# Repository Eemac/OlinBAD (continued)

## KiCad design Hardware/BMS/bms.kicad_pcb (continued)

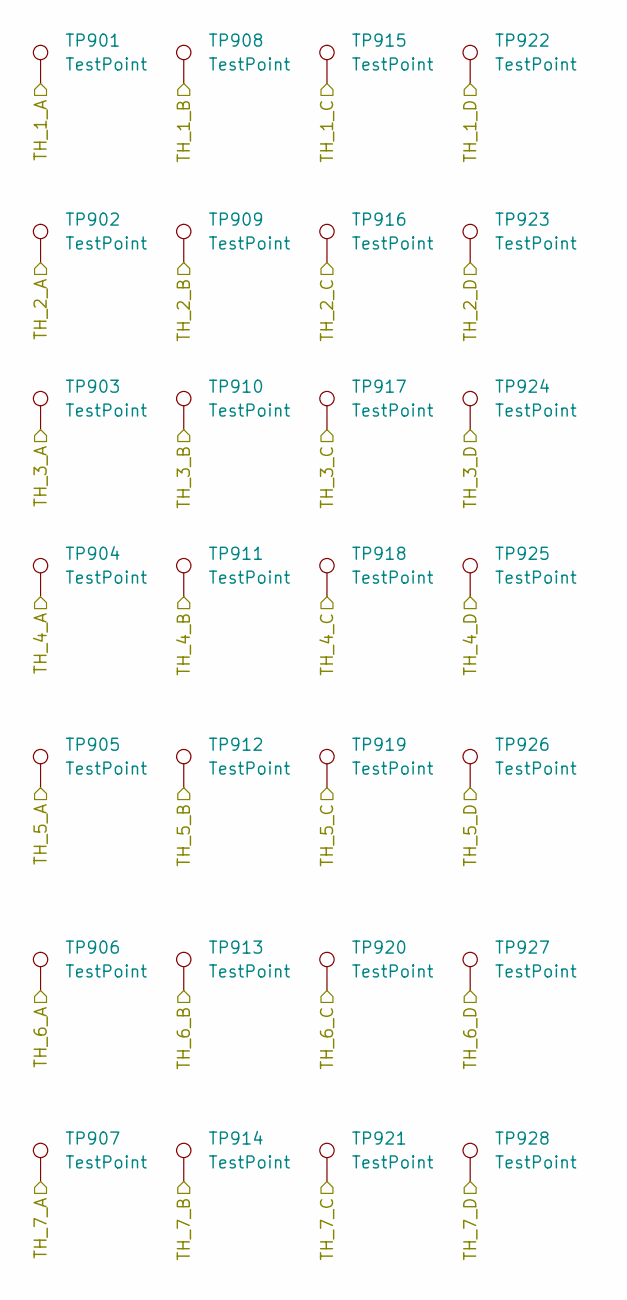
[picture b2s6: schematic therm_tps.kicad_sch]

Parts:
TP901, TP902, TP903, TP904, TP905, TP906, TP907, TP908, TP909, TP910, TP911, TP912, TP913, TP914, TP915, TP916, TP917, TP918, TP919, TP920, TP921, TP922, TP923, TP924, TP925, TP926, TP927, TP928: TestPoint; TestPoint_Pad_1.0x1.0mm

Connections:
/Thermistors/TH_1_A: TP901.1; also elsewhere on the board
/Thermistors/TH_1_B: TP908.1; also elsewhere on the board
/Thermistors/TH_1_C: TP915.1; also elsewhere on the board
/Thermistors/TH_1_D: TP922.1; also elsewhere on the board
/Thermistors/TH_2_A: TP902.1; also elsewhere on the board
/Thermistors/TH_2_B: TP909.1; also elsewhere on the board
/Thermistors/TH_2_C: TP916.1; also elsewhere on the board
/Thermistors/TH_2_D: TP923.1; also elsewhere on the board
/Thermistors/TH_3_A: TP917.1; also elsewhere on the board
/Thermistors/TH_3_B: TP924.1; also elsewhere on the board
/Thermistors/TH_3_C: TP903.1; also elsewhere on the board
/Thermistors/TH_3_D: TP910.1; also elsewhere on the board
/Thermistors/TH_4_A: TP904.1; also elsewhere on the board
/Thermistors/TH_4_B: TP911.1; also elsewhere on the board
/Thermistors/TH_4_C: TP918.1; also elsewhere on the board
/Thermistors/TH_4_D: TP925.1; also elsewhere on the board
/Thermistors/TH_5_A: TP905.1; also elsewhere on the board
/Thermistors/TH_5_B: TP912.1; also elsewhere on the board
/Thermistors/TH_5_C: TP919.1; also elsewhere on the board
/Thermistors/TH_5_D: TP926.1; also elsewhere on the board
/Thermistors/TH_6_A: TP906.1; also elsewhere on the board
/Thermistors/TH_6_B: TP913.1; also elsewhere on the board
/Thermistors/TH_6_C: TP920.1; also elsewhere on the board
/Thermistors/TH_6_D: TP927.1; also elsewhere on the board
/Thermistors/TH_7_A: TP907.1; also elsewhere on the board
/Thermistors/TH_7_B: TP914.1; also elsewhere on the board
/Thermistors/TH_7_C: TP921.1; also elsewhere on the board
/Thermistors/TH_7_D: TP928.1; also elsewhere on the board

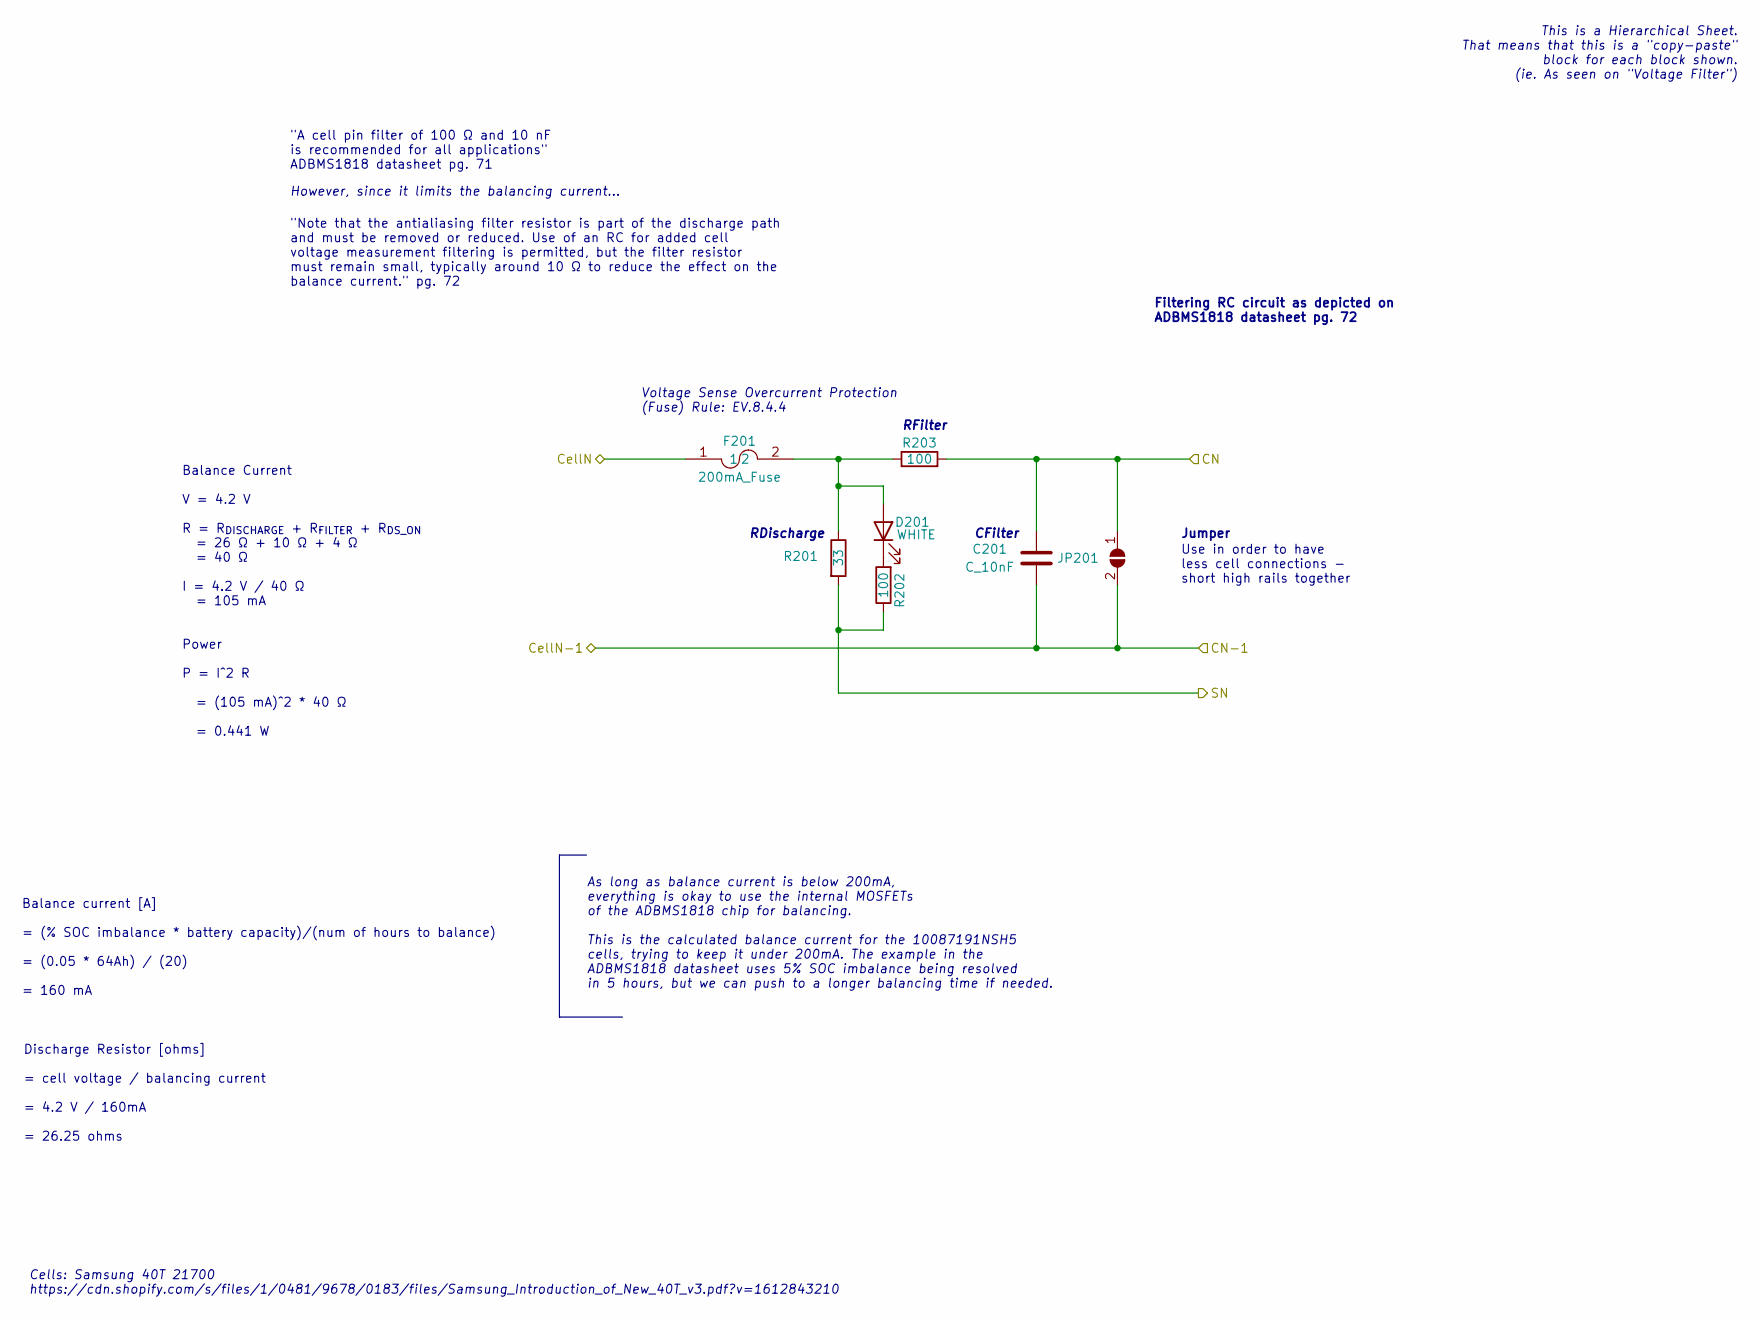
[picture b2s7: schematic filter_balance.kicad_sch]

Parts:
C201: C_10nF; C_0603_1608Metric; MPN CL10B103KB8NNNC
D201: WHITE; LED_0805_2012Metric
F201: 200mA_Fuse; Fuse_1206_3216Metric; MPN 0466.200NRHF
JP201: SolderJumper_2_Open; SolderJumper-2_P1.3mm_Open_TrianglePad1.0x1.5mm
R201: 33; R_2512_6332Metric; MPN 352022RJT
R202: 100; R_0603_1608Metric
R203: 100; R_0603_1608Metric; MPN SG73P1JTTD100J

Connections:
/ADBMS1818/C1: C201.1, F201.1, JP201.1 (A), R203.2; also elsewhere on the board
/ADBMS1818/S1: R201.2, R202.1; also elsewhere on the board
GND: C201.2, JP201.2 (B); also elsewhere on the board
unnamed: D201.2 (A), F201.2, R201.1, R203.1
unnamed: D201.1 (K), R202.2

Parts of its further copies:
C701, C1001, C1201, C1301, C1401, C1501, C1601, C1701, C1801, C1901, C2001, C2101, C2201: C_10nF; C_0603_1608Metric; MPN CL10B103KB8NNNC
D701, D1001, D1201, D1301, D1401, D1501, D1601, D1701, D1801, D1901, D2001, D2101, D2201: WHITE; LED_0805_2012Metric
F701, F1001, F1201, F1301, F1401, F1501, F1601, F1701, F1801, F1901, F2001, F2101, F2201: 200mA_Fuse; Fuse_1206_3216Metric; MPN 0466.200NRHF
JP701, JP1001, JP1201, JP1301, JP1401, JP1501, JP1601, JP1701, JP1801, JP1901, JP2001, JP2101, JP2201: SolderJumper_2_Open; SolderJumper-2_P1.3mm_Open_TrianglePad1.0x1.5mm
R701, R1001, R1201, R1301, R1401, R1501, R1601, R1701, R1801, R1901, R2001, R2101, R2201: 33; R_2512_6332Metric; MPN 352022RJT
R702, R1002, R1202, R1302, R1402, R1502, R1602, R1702, R1802, R1902, R2002, R2102, R2202: 100; R_0603_1608Metric
R703, R1003, R1203, R1303, R1403, R1503, R1603, R1703, R1803, R1903, R2003, R2103, R2203: 100; R_0603_1608Metric; MPN SG73P1JTTD100J

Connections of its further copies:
/ADBMS1818/C1: C701.2, JP701.2 (B); also elsewhere on the board
/ADBMS1818/C2: C701.1, C1001.2, F701.1, JP701.1 (A), JP1001.2 (B), R703.2; also elsewhere on the board
/ADBMS1818/C3: C1001.1, C1201.2, F1001.1, JP1001.1 (A), JP1201.2 (B), R1003.2; also elsewhere on the board
/ADBMS1818/C4: C1201.1, C1301.2, F1201.1, JP1201.1 (A), JP1301.2 (B), R1203.2; also elsewhere on the board
/ADBMS1818/C5: C1301.1, C1401.2, F1301.1, JP1301.1 (A), JP1401.2 (B), R1303.2; also elsewhere on the board
/ADBMS1818/C6: C1401.1, C1501.2, F1401.1, JP1401.1 (A), JP1501.2 (B), R1403.2; also elsewhere on the board
/ADBMS1818/C7: C1501.1, C1601.2, F1501.1, JP1501.1 (A), JP1601.2 (B), R1503.2; also elsewhere on the board
/ADBMS1818/C8: C1601.1, C1701.2, F1601.1, JP1601.1 (A), JP1701.2 (B), R1603.2; also elsewhere on the board
/ADBMS1818/C9: C1701.1, C1801.2, F1701.1, JP1701.1 (A), JP1801.2 (B), R1703.2; also elsewhere on the board
/ADBMS1818/C10: C1801.1, C1901.2, F1801.1, JP1801.1 (A), JP1901.2 (B), R1803.2; also elsewhere on the board
/ADBMS1818/C11: C1901.1, C2001.2, F1901.1, JP1901.1 (A), JP2001.2 (B), R1903.2; also elsewhere on the board
/ADBMS1818/C12: C2001.1, C2101.2, F2001.1, JP2001.1 (A), JP2101.2 (B), R2003.2; also elsewhere on the board
/ADBMS1818/C13: C2101.1, C2201.2, F2101.1, JP2101.1 (A), JP2201.2 (B), R2103.2; also elsewhere on the board
/ADBMS1818/C14: C2201.1, JP2201.1 (A), R2203.2; also elsewhere on the board
/ADBMS1818/CELL14: F2201.1; also elsewhere on the board
/ADBMS1818/S2: R701.2, R702.1; also elsewhere on the board
/ADBMS1818/S3: R1001.2, R1002.1; also elsewhere on the board
/ADBMS1818/S4: R1201.2, R1202.1; also elsewhere on the board
/ADBMS1818/S5: R1301.2, R1302.1; also elsewhere on the board
/ADBMS1818/S6: R1401.2, R1402.1; also elsewhere on the board
/ADBMS1818/S7: R1501.2, R1502.1; also elsewhere on the board
/ADBMS1818/S8: R1601.2, R1602.1; also elsewhere on the board
/ADBMS1818/S9: R1701.2, R1702.1; also elsewhere on the board
/ADBMS1818/S10: R1801.2, R1802.1; also elsewhere on the board
/ADBMS1818/S11: R1901.2, R1902.1; also elsewhere on the board
/ADBMS1818/S12: R2001.2, R2002.1; also elsewhere on the board
/ADBMS1818/S13: R2101.2, R2102.1; also elsewhere on the board
/ADBMS1818/S14: R2201.2, R2202.1; also elsewhere on the board
unnamed: D701.2 (A), F701.2, R701.1, R703.1
unnamed: D701.1 (K), R702.2
unnamed: D1001.2 (A), F1001.2, R1001.1, R1003.1
unnamed: D1001.1 (K), R1002.2
unnamed: D1201.2 (A), F1201.2, R1201.1, R1203.1
unnamed: D1201.1 (K), R1202.2
unnamed: D1301.2 (A), F1301.2, R1301.1, R1303.1
unnamed: D1301.1 (K), R1302.2
unnamed: D1401.2 (A), F1401.2, R1401.1, R1403.1
unnamed: D1401.1 (K), R1402.2
unnamed: D1501.2 (A), F1501.2, R1501.1, R1503.1
unnamed: D1501.1 (K), R1502.2
unnamed: D1601.2 (A), F1601.2, R1601.1, R1603.1
unnamed: D1601.1 (K), R1602.2
unnamed: D1701.2 (A), F1701.2, R1701.1, R1703.1
unnamed: D1701.1 (K), R1702.2
unnamed: D1801.2 (A), F1801.2, R1801.1, R1803.1
unnamed: D1801.1 (K), R1802.2
unnamed: D1901.2 (A), F1901.2, R1901.1, R1903.1
unnamed: D1901.1 (K), R1902.2
unnamed: D2001.2 (A), F2001.2, R2001.1, R2003.1
unnamed: D2001.1 (K), R2002.2
unnamed: D2101.2 (A), F2101.2, R2101.1, R2103.1
unnamed: D2101.1 (K), R2102.2
unnamed: D2201.2 (A), F2201.2, R2201.1, R2203.1
unnamed: D2201.1 (K), R2202.2

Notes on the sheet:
Filtering RC circuit as depicted on ADBMS1818 datasheet pg. 72
"A cell pin filter of 100 Ω and 10 nF is recommended for all applications" ADBMS1818 datasheet pg. 71
Cells: Samsung 40T 21700 https://cdn.shopify.com/s/files/1/0481/9678/0183/files/Samsung_Introduction_of_New_40T_v3.pdf?v=1612843210
Balance current [A] = (% SOC imbalance * battery capacity)/(num of hours to balance) = (0.05 * 64Ah) / (20) = 160 mA
RFilter
Discharge Resistor [ohms] = cell voltage / balancing current = 4.2 V / 160mA = 26.25 ohms
Use in order to have less cell connections - short high rails together
"Note that the antialiasing filter resistor is part of the discharge path and must be removed or reduced. Use of an RC for added cell voltage measurement filtering is permitted, but the filter resistor must remain small, typically around 10 Ω to reduce the effect on the balance current." pg. 72
However, since it limits the balancing current...
RDischarge
Balance Current V = 4.2 V R = R_{DISCHARGE} + R_{FILTER} + R_{DS_ON} = 26 Ω + 10 Ω + 4 Ω = 40 Ω I = 4.2 V / 40 Ω = 105 mA Power P = I^2 R = (105 mA)^2 * 40 Ω = 0.441 W
As long as balance current is below 200mA, everything is okay to use the internal MOSFETs of the ADBMS1818 chip for balancing. This is the calculated balance current for the 10087191NSH5 cells, trying to keep it under 200mA. The example in the ADBMS1818 datasheet uses 5% SOC imbalance being resolve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
This is a Hierarchical Sheet. That means that this is a "copy-paste" block for each block shown. (ie. As seen on "Voltage Filter")
CFilter
Voltage Sense Overcurrent Protection (Fuse) Rule: EV.8.4.4
Jumper

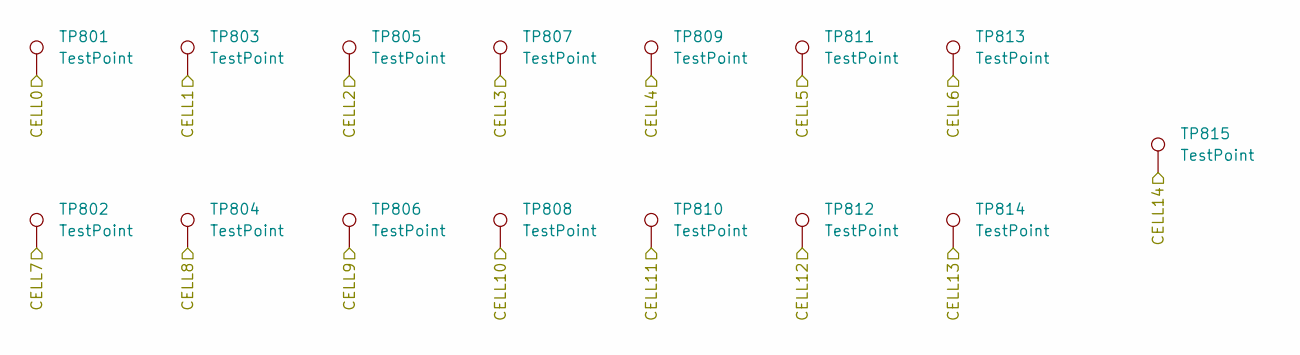
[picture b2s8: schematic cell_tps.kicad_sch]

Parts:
TP801, TP802, TP803, TP804, TP805, TP806, TP807, TP808, TP809, TP810, TP811, TP812, TP813, TP814, TP815: TestPoint; TestPoint_Pad_1.0x1.0mm

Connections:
/ADBMS1818/C1: TP803.1; also elsewhere on the board
/ADBMS1818/C2: TP805.1; also elsewhere on the board
/ADBMS1818/C3: TP807.1; also elsewhere on the board
/ADBMS1818/C4: TP809.1; also elsewhere on the board
/ADBMS1818/C5: TP811.1; also elsewhere on the board
/ADBMS1818/C6: TP813.1; also elsewhere on the board
/ADBMS1818/C7: TP802.1; also elsewhere on the board
/ADBMS1818/C8: TP804.1; also elsewhere on the board
/ADBMS1818/C9: TP806.1; also elsewhere on the board
/ADBMS1818/C10: TP808.1; also elsewhere on the board
/ADBMS1818/C11: TP810.1; also elsewhere on the board
/ADBMS1818/C12: TP812.1; also elsewhere on the board
/ADBMS1818/C13: TP814.1; also elsewhere on the board
/ADBMS1818/CELL14: TP815.1; also elsewhere on the board
GND: TP801.1; also elsewhere on the board

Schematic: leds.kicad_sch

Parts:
D1101, D1104, D1106, D1109, D1111: LED_0805_Red; LED_0805_OEM; MPN 475-1415-1-ND
D1102, D1105, D1108, D1110, D1112: LED_0805; LED_0805_OEM; MPN 475-1410-1-ND
D1103, D1107: LED_0805_Amber; LED_0805_OEM; MPN L71517CT-ND
R1101, R1104, R1106, R1109, R1111: 300; R_0603_1608Metric; MPN 667-ERJ-6ENF1200V
R1102, R1105, R1108, R1110, R1112: 120; R_0603_1608Metric; MPN 667-ERJ-6ENF1200V
R1103, R1107: 220; R_0603_1608Metric; MPN 667-ERJ-6ENF1200V

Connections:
/STM32/ADBMS_COMS: D1110.2 (A); also elsewhere on the board
/STM32/BMS_HEARTBEAT: D1107.2 (A); also elsewhere on the board
/STM32/CAN_COMS: D1102.2 (A); also elsewhere on the board
/STM32/DEBUG1: D1103.2 (A); also elsewhere on the board
/STM32/ERROR: D1111.2 (A); also elsewhere on the board
/STM32/MUX1_COMS: D1105.2 (A); also elsewhere on the board
/STM32/MUX2_COMS: D1108.2 (A); also elsewhere on the board
/STM32/OT: D1106.2 (A); also elsewhere on the board
/STM32/OV: D1101.2 (A); also elsewhere on the board
/STM32/USB_C_COMS: D1112.2 (A); also elsewhere on the board
/STM32/UT: D1109.2 (A); also elsewhere on the board
/STM32/UV: D1104.2 (A); also elsewhere on the board
GND: R1101.2, R1102.2, R1103.2, R1104.2, R1105.2, R1106.2, R1107.2, R1108.2, R1109.2, R1110.2, R1111.2, R1112.2; also elsewhere on the board
unnamed: D1101.1 (K), R1101.1
unnamed: D1102.1 (K), R1102.1
unnamed: D1103.1 (K), R1103.1
unnamed: D1104.1 (K), R1104.1
unnamed: D1105.1 (K), R1105.1
unnamed: D1106.1 (K), R1106.1
unnamed: D1107.1 (K), R1107.1
unnamed: D1108.1 (K), R1108.1
unnamed: D1109.1 (K), R1109.1
unnamed: D1110.1 (K), R1110.1
unnamed: D1111.1 (K), R1111.1
unnamed: D1112.1 (K), R1112.1

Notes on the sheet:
Heartbeat in code

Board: 4 copper layers, 316 parts (0 on the bottom side), 181 nets, no tracks yet.

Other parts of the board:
kibuzzard-68FE96E6: G***; kibuzzard-68FE96E6
kibuzzard-68FE9694: G***; kibuzzard-68FE9694
kibuzzard-68FE9708: G***; kibuzzard-68FE9708

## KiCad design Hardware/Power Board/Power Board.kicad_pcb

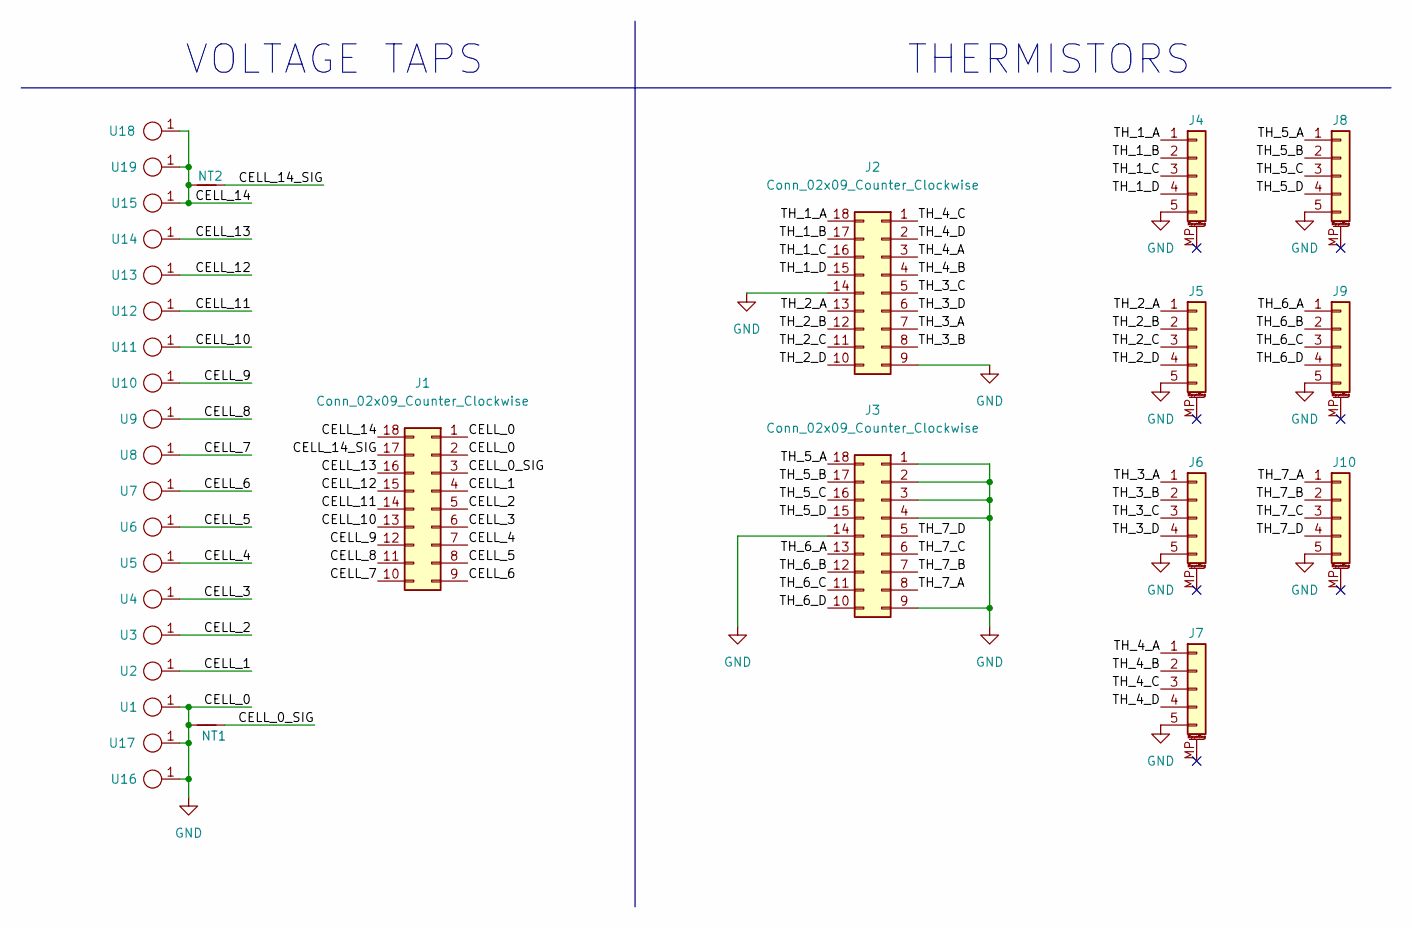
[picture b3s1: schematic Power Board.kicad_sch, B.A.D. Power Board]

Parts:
J1, J2, J3: Conn_02x09_Counter_Clockwise; PinSocket_2x09_P2.54mm_Vertical
J4, J5, J6, J7, J8, J9, J10: Conn_01x05_MountingPin; TE_0-1734839-5_1x05-1MP_P0.5mm_Horizontal
NT1, NT2: NetTie_2; NetTie-2_SMD_Pad0.5mm
U1, U2, U3, U4, U5, U6, U7, U8, U9, U10, U11, U12, U13, U14, U15: BatteryTab
U16, U17, U18, U19: 7461098

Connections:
/CELL_0_SIG: J1.3, NT1.2
/CELL_1: J1.4, U2.1
/CELL_2: J1.5, U3.1
/CELL_3: J1.6, U4.1
/CELL_4: J1.7, U5.1
/CELL_5: J1.8, U6.1
/CELL_6: J1.9, U7.1
/CELL_7: J1.10, U8.1
/CELL_8: J1.11, U9.1
/CELL_9: J1.12, U10.1
/CELL_10: J1.13, U11.1
/CELL_11: J1.14, U12.1
/CELL_12: J1.15, U13.1
/CELL_13: J1.16, U14.1
/CELL_14: J1.18, NT2.2, U15.1, U18.1, U19.1
/CELL_14_SIG: J1.17, NT2.1
/TH_1_A: J2.18, J4.1
/TH_1_B: J2.17, J4.2
/TH_1_C: J2.16, J4.3
/TH_1_D: J2.15, J4.4
/TH_2_A: J2.13, J5.1
/TH_2_B: J2.12, J5.2
/TH_2_C: J2.11, J5.3
/TH_2_D: J2.10, J5.4
/TH_3_A: J2.7, J6.1
/TH_3_B: J2.8, J6.2
/TH_3_C: J2.5, J6.3
/TH_3_D: J2.6, J6.4
/TH_4_A: J2.3, J7.1
/TH_4_B: J2.4, J7.2
/TH_4_C: J2.1, J7.3
/TH_4_D: J2.2, J7.4
/TH_5_A: J3.18, J8.1
/TH_5_B: J3.17, J8.2
/TH_5_C: J3.16, J8.3
/TH_5_D: J3.15, J8.4
/TH_6_A: J3.13, J9.1
/TH_6_B: J3.12, J9.2
/TH_6_C: J3.11, J9.3
/TH_6_D: J3.10, J9.4
/TH_7_A: J3.8, J10.1
/TH_7_B: J3.7, J10.2
/TH_7_C: J3.6, J10.3
/TH_7_D: J3.5, J10.4
GND: J1.1, J1.2, J2.9, J2.14, J3.1, J3.2, J3.3, J3.4, J3.9, J3.14, J4.5, J5.5, J6.5, J7.5, J8.5, J9.5, J10.5, NT1.1, U1.1, U16.1, U17.1

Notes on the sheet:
THERMISTORS
VOLTAGE TAPS

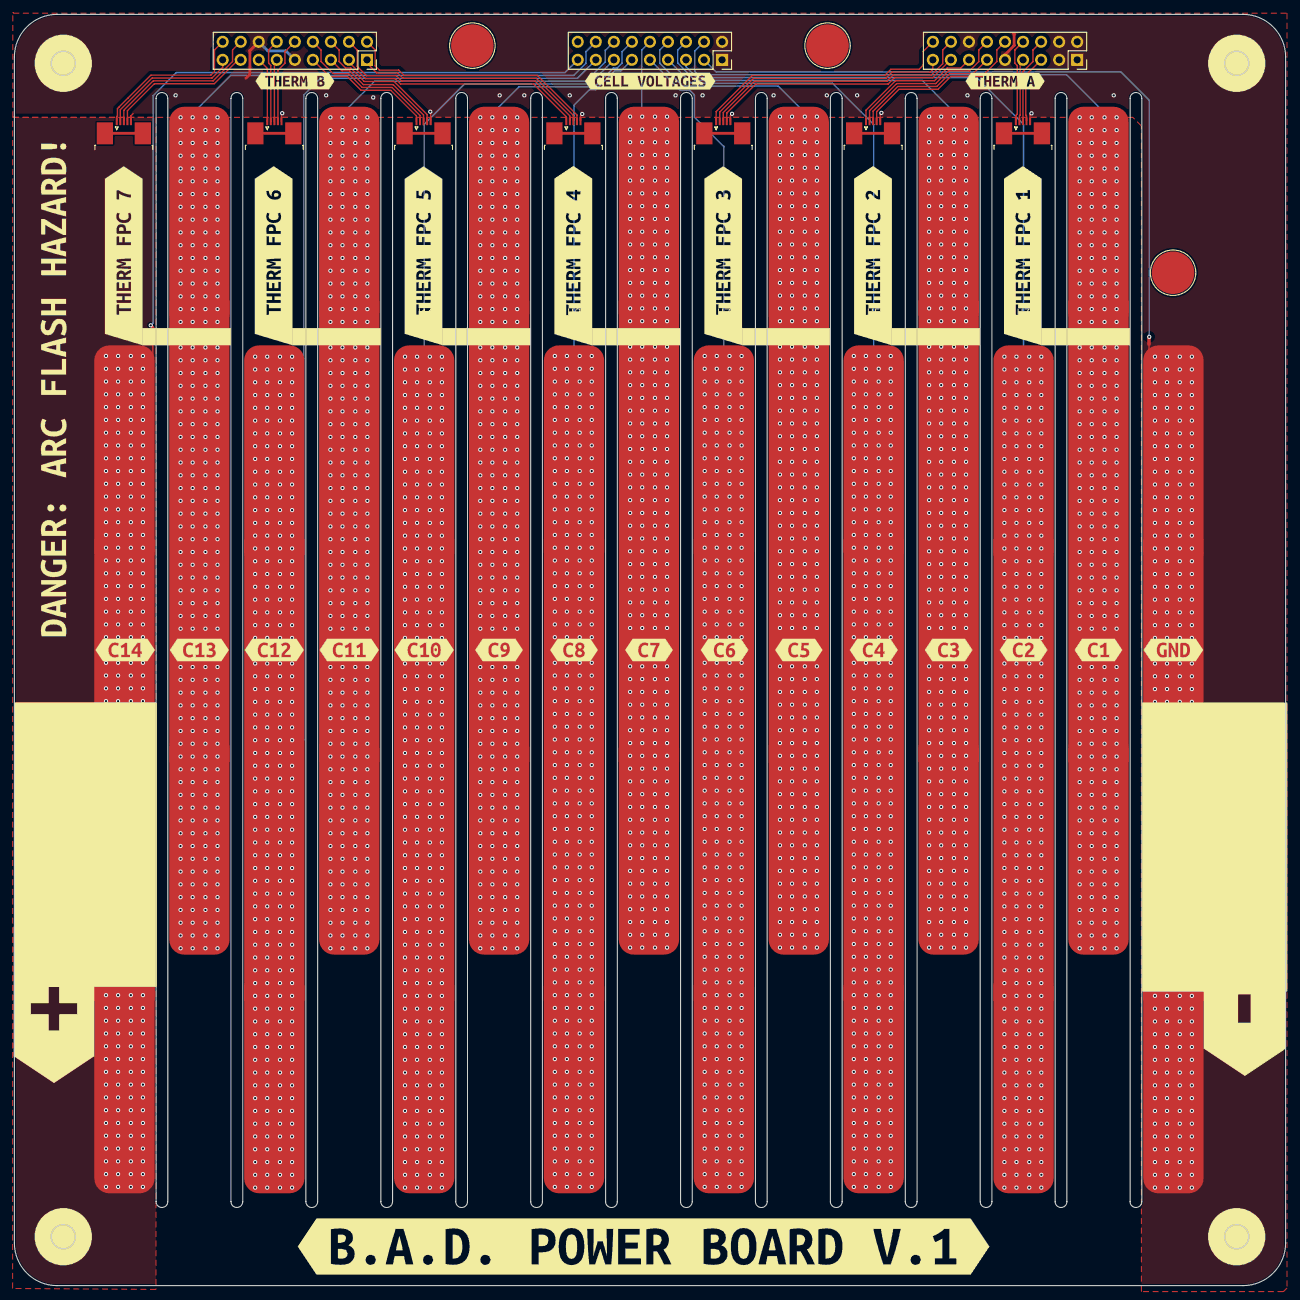
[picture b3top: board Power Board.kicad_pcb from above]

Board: 2 copper layers, 179.0 x 179.0 mm, 60 parts (0 on the bottom side), 45 nets.

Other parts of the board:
kibuzzard-68FE6C25: G***; kibuzzard-68FE6C25
kibuzzard-68FE8B33: G***; kibuzzard-68FE8B33
kibuzzard-68FE8BAD: G***; kibuzzard-68FE8BAD
kibuzzard-68FE8C3A: G***; kibuzzard-68FE8C3A
kibuzzard-68FE8C6B: G***; kibuzzard-68FE8C6B
kibuzzard-68FE8C6F: G***; kibuzzard-68FE8C6F
kibuzzard-68FE8C7B: G***; kibuzzard-68FE8C7B
kibuzzard-68FE8C8C: G***; kibuzzard-68FE8C8C
kibuzzard-68FE8C9C: G***; kibuzzard-68FE8C9C
kibuzzard-68FE8C40: G***; kibuzzard-68FE8C40
kibuzzard-68FE8C46: G***; kibuzzard-68FE8C46
kibuzzard-68FE8C51: G***; kibuzzard-68FE8C51
kibuzzard-68FE8C58: G***; kibuzzard-68FE8C58
kibuzzard-68FE8C80: G***; kibuzzard-68FE8C80
kibuzzard-68FE8C86: G***; kibuzzard-68FE8C86
kibuzzard-68FE8C91: G***; kibuzzard-68FE8C91
kibuzzard-68FE8C96: G***; kibuzzard-68FE8C96
kibuzzard-68FE9A02: G***; kibuzzard-68FE9A02
kibuzzard-68FE96E6: G***; kibuzzard-68FE96E6
kibuzzard-68FE971D: G***; kibuzzard-68FE971D
kibuzzard-68FE972D: G***; kibuzzard-68FE972D
kibuzzard-68FE9694: G***; kibuzzard-68FE9694
kibuzzard-68FE9708: G***; kibuzzard-68FE9708
kibuzzard-68FE9722: G***; kibuzzard-68FE9722
kibuzzard-68FE9727: G***; kibuzzard-68FE9727
kibuzzard-68FE9731: G***; kibuzzard-68FE9731
kibuzzard-68FE9739: G***; kibuzzard-68FE9739
kibuzzard-68FE9876: G***; kibuzzard-68FE9876
kibuzzard-68FEE0E1: G***; kibuzzard-68FEE0E1

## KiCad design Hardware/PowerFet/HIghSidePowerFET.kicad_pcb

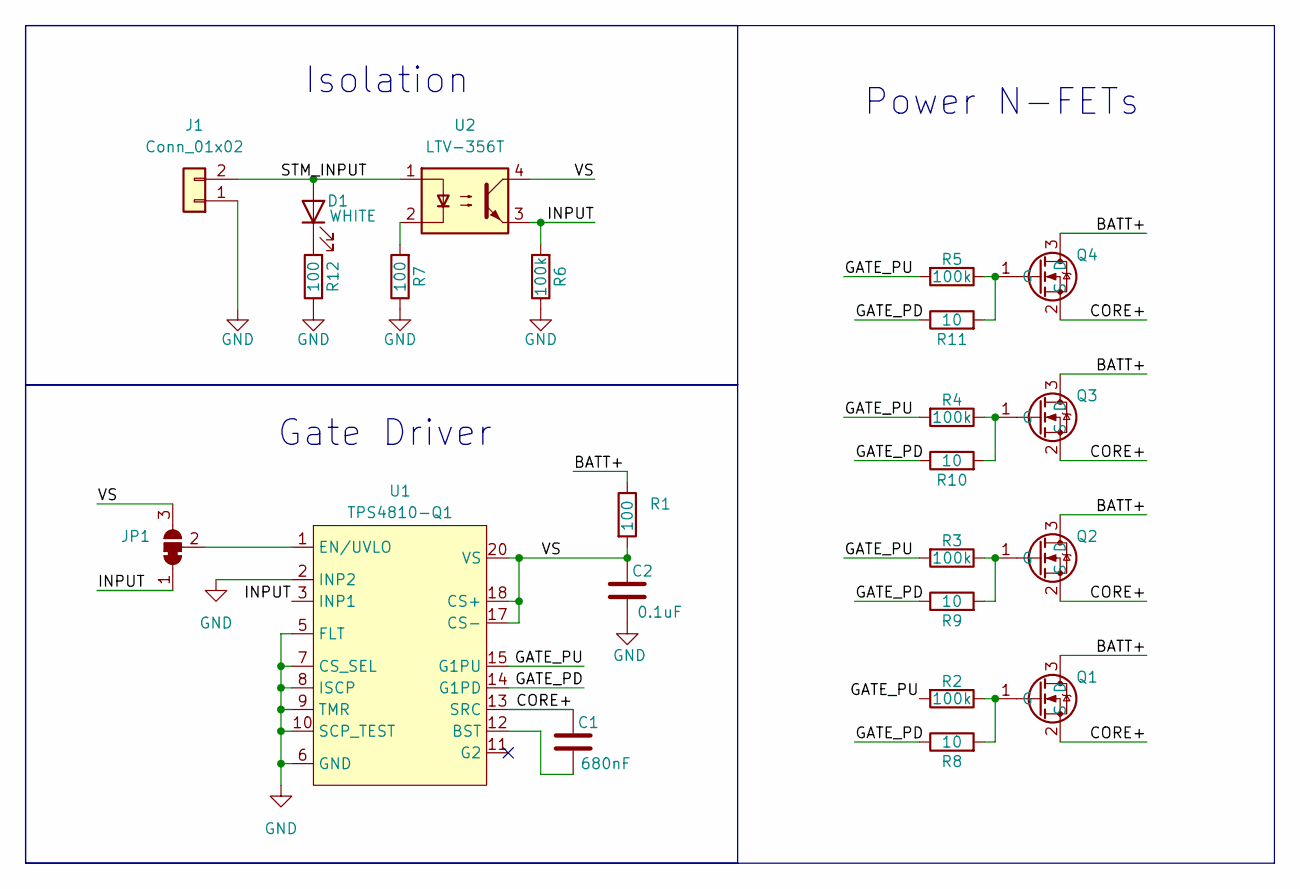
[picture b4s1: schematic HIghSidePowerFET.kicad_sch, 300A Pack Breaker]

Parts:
C1: 680nF; C_0603_1608Metric
C2: 0.1uF; C_0603_1608Metric
D1: WHITE; LED_0805_2012Metric
J1: Conn_01x02; Molex_Nano-Fit_105313-xx02_1x02_P2.50mm_Horizontal
JP1: SolderJumper_3_Bridged12; SolderJumper-3_P1.3mm_Bridged12_RoundedPad1.0x1.5mm
Q1, Q2, Q3, Q4: NTBLS0D8N08X
R1: 100; R_0805_2012Metric
R2, R3, R4, R5, R6: 100k; R_0603_1608Metric
R7, R12: 100; R_0603_1608Metric
R8, R9, R10, R11: 10; R_0603_1608Metric
U1: TPS4810-Q1; VSSOP-19
U2: LTV-356T; SO-4_4.4x3.6mm_P2.54mm

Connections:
/BATT+: Q1.3 (D), Q2.3 (D), Q3.3 (D), Q4.3 (D), R1.1
/CORE+: C1.2, Q1.2 (S), Q2.2 (S), Q3.2 (S), Q4.2 (S), U1.13 (SRC)
/GATE_PD: R8.1, R9.1, R10.1, R11.1, U1.14 (G1PD)
/GATE_PU: R2.2, R3.2, R4.2, R5.2, U1.15 (G1PU)
/INPUT: JP1.1 (A), R6.2, U1.3 (INP1), U2.3
/STM_INPUT: D1.2 (A), J1.2, U2.1
/VS: C2.2, JP1.3 (B), R1.2, U1.17 (CS-), U1.18 (CS+), U1.20 (VS), U2.4
GND: C2.1, J1.1, R6.1, R7.1, R12.1, U1.2 (INP2), U1.5 (FLT), U1.6 (GND), U1.7 (CS_SEL), U1.8 (ISCP), U1.9 (TMR), U1.10 (SCP_TEST)
unnamed: D1.1 (K), R12.2
unnamed: JP1.2 (C), U1.1 (EN/UVLO)
unnamed: Q1.1 (G), R2.1, R8.2
unnamed: Q2.1 (G), R3.1, R9.2
unnamed: Q3.1 (G), R4.1, R10.2
unnamed: Q4.1 (G), R5.1, R11.2
unnamed: R7.2, U2.2
unnamed: C1.1, U1.12 (BST)

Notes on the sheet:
Power N-FETs
Gate Driver
Isolation

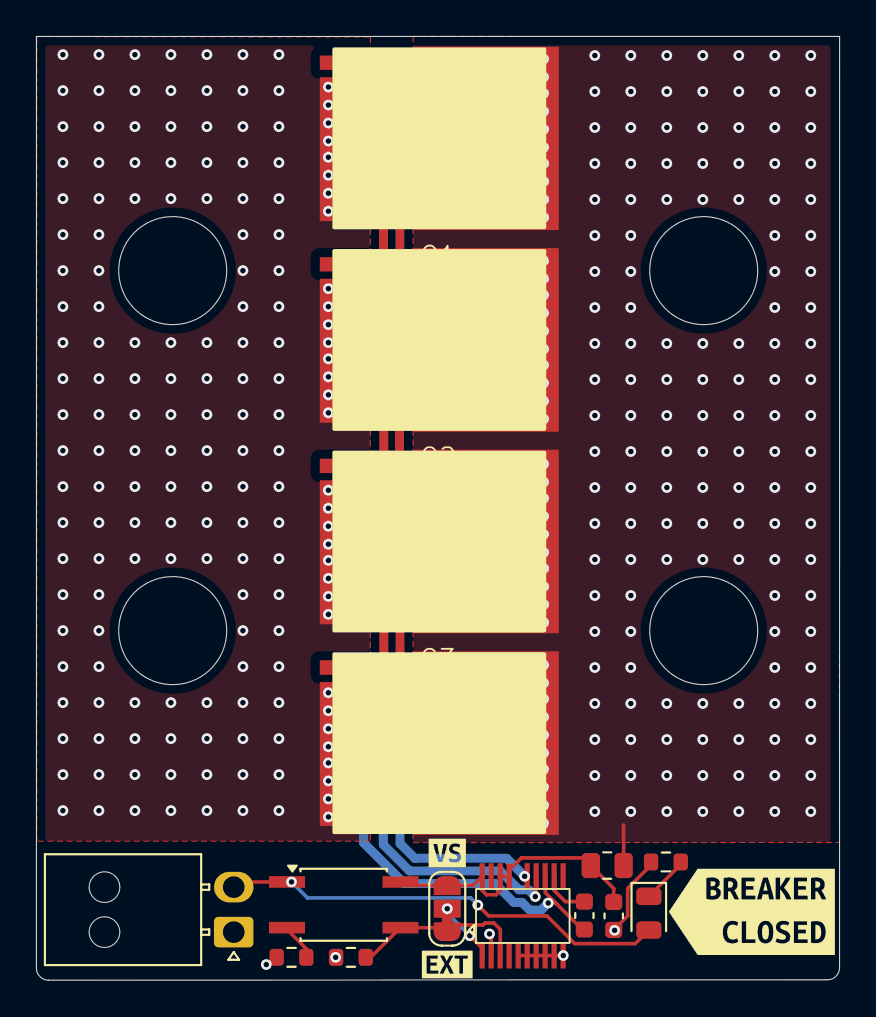
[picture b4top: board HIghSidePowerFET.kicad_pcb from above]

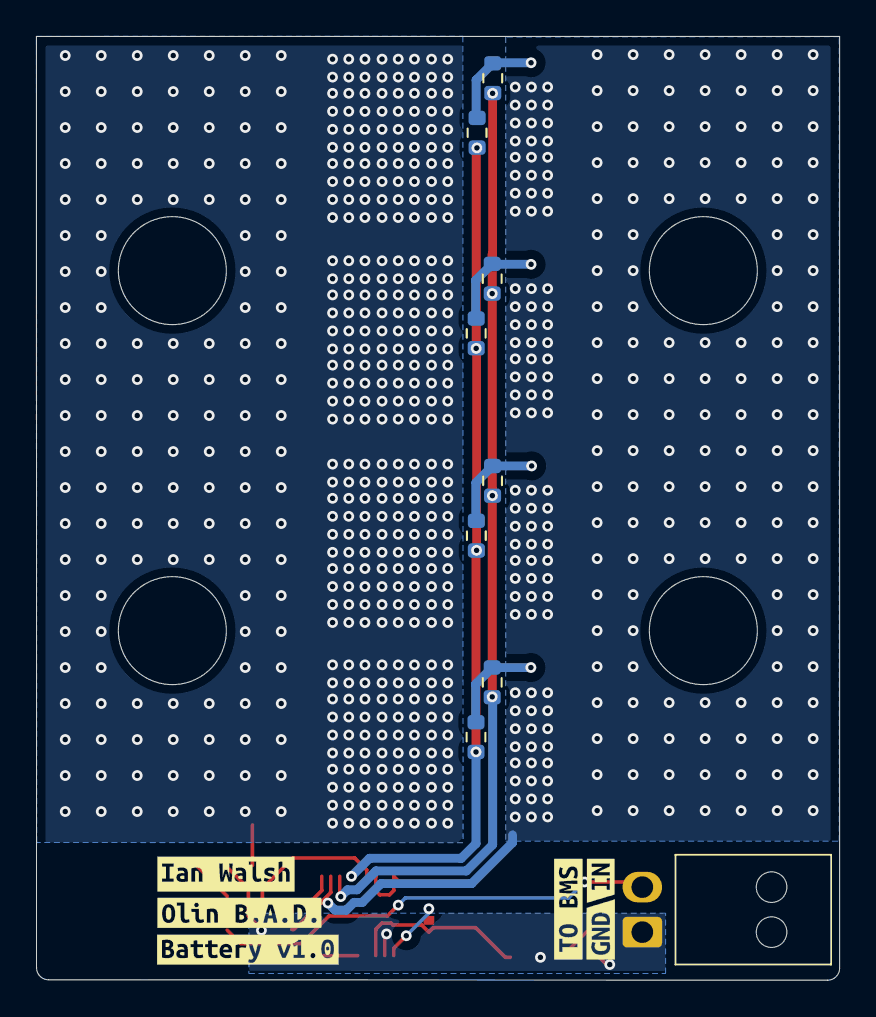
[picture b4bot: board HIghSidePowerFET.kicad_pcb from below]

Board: 2 copper layers, 44.6 x 52.4 mm, 32 parts (14 on the bottom side), 16 nets.

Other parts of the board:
kibuzzard-68F7A0AD: G***; kibuzzard-68F7A0AD
kibuzzard-68F7A0C5: G***; kibuzzard-68F7A0C5
kibuzzard-68F7A12F: G***; kibuzzard-68F7A12F
kibuzzard-68F7ACD6: G***; kibuzzard-68F7ACD6
kibuzzard-68F7AD8A: G***; kibuzzard-68F7AD8A
kibuzzard-68F7ADA7: G***; kibuzzard-68F7ADA7
kibuzzard-68F7D5F0: G***; kibuzzard-68F7D5F0
kibuzzard-68F79DB8: G***; kibuzzard-68F79DB8
kibuzzard-68F79DC8: G***; kibuzzard-68F79DC8

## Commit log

2025-10-07 inital file structure
2025-10-08 added kicad lib files
2025-10-10 adding formula symbol lib + oem.pretty + formula.pretty + 6 pin molex RA connectors
2025-10-10 associating minifit symbol with footprint and changing symbol
2025-10-10 added 4 bms connectors and unfinished stm32 peripherals subsheet draft
2025-10-10 deleting autosave files
2025-10-27 power + fet baord added
2025-10-29 edits to the BMS
2025-10-29 added can transciever
2025-10-29 add in comm protocols
2025-10-29 save
2025-10-29 updated some stm stuff and added current sense amplifier for main pack
2025-10-29 adding gitignore
2025-10-29 added df17 part to library, added stm32 actual names of pins
2025-10-29 adding cube connector
2025-10-29 Add test points and LEDs
2025-10-31 added gitignore to get rid of extra kicad files
2025-10-31 removing .DS_Store files
2025-10-31 begin layout
2025-11-01 some pcb layout
2025-11-01 Initial Thermistor geo
2025-11-01 adding logic gate symbols, moving cube+ symbol to libraries folder, deleting duplicate formula libs
2025-11-01 getting rid of files that are now in our gitignore
2025-11-01 adding logic gate and cube orange footprints to obad lib
